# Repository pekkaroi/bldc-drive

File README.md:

# bldc-drive

This is a project developing a simple BLDC servo controller. It is based on an STM32F103 microcontroller.

Some parts, especially the PID control loop is based on development done by user mcm_xyz in cnczone.com forum. Thank you! Check the thread http://www.cnczone.com/forums/open-source-controller-boards/283428-cnc.html 

## Disclaimer
This software and hardware is provided "AS IS", WITHOUT ANY WARRANTY. The software is released under GPL v2. Authors accept no liability for any harm or loss resulting from use of this hardware or software.

## Authors & Contributors
* original Software by mcm_xyz from cnczone
* first Version of Hardware&Software in a Git-repo from pekkaroi via https://github.com/pekkaroi
* Schematic-additions and fork by Philipp Hörauf via https://github.com/Virtex7

## Firmware
Firmware is a work-in-progress (and will be for a while :), however following features are included:
* Trapezoidal BLDC commutation using either HALL sensors or quadrature encoder.
* Step+Dir input interface with PID position control loop.
* PWM+Dir input interface in velocity mode.
* USART communitacation for configuration. Configuration settings saved to flash memory.
* TODO: Motor Test Mode to simply activate a Motor with a fixed frequency, no encoder needed

### Update 1st May 2016
Some updates to the firmware. 
* ADC current limiting implemented. Appears to work OK
* I created a quick and ugly Python gui for tuning
* Updated the PID loop to have feedfoward coefficients FF1 and FF2 (like LinuxCNC). This means that the PID output can be adjusted by the requested speed and the requested acceleration. This made the PID tuning a lot easier for me at least, I'm able to get a motor to follow the requested position very well also during acceleration and during constant drive.

## Hardware:
First prototype hardware is built and it is working well. However, there are couple of known issues:
* 6n137 optocoupler is not officially supporting 3.3V supply voltage which is used in the board. In reality they seem to work, but the optocoupler should be changed or additional levelshifting circuitry added on next revision. Also, the optocoupler input circuit supports only push-pull-type encoder output. Many encoders seem to have open drain output. :(
* Few connectors in the layout missed solder stop openings. They were bit painfull to solder. :)
* The current amplifier INA27x connection is wrong. The IN+ and IN- should be swapped.

### STATUS QUO:

Second hardware revision with the above findings fixed is published. There are no known issues, two servo drives are succesfully driving my CNC router. Pics and videos to come..

### HARDWARE TODOs:

* verify all part-values into the schematic

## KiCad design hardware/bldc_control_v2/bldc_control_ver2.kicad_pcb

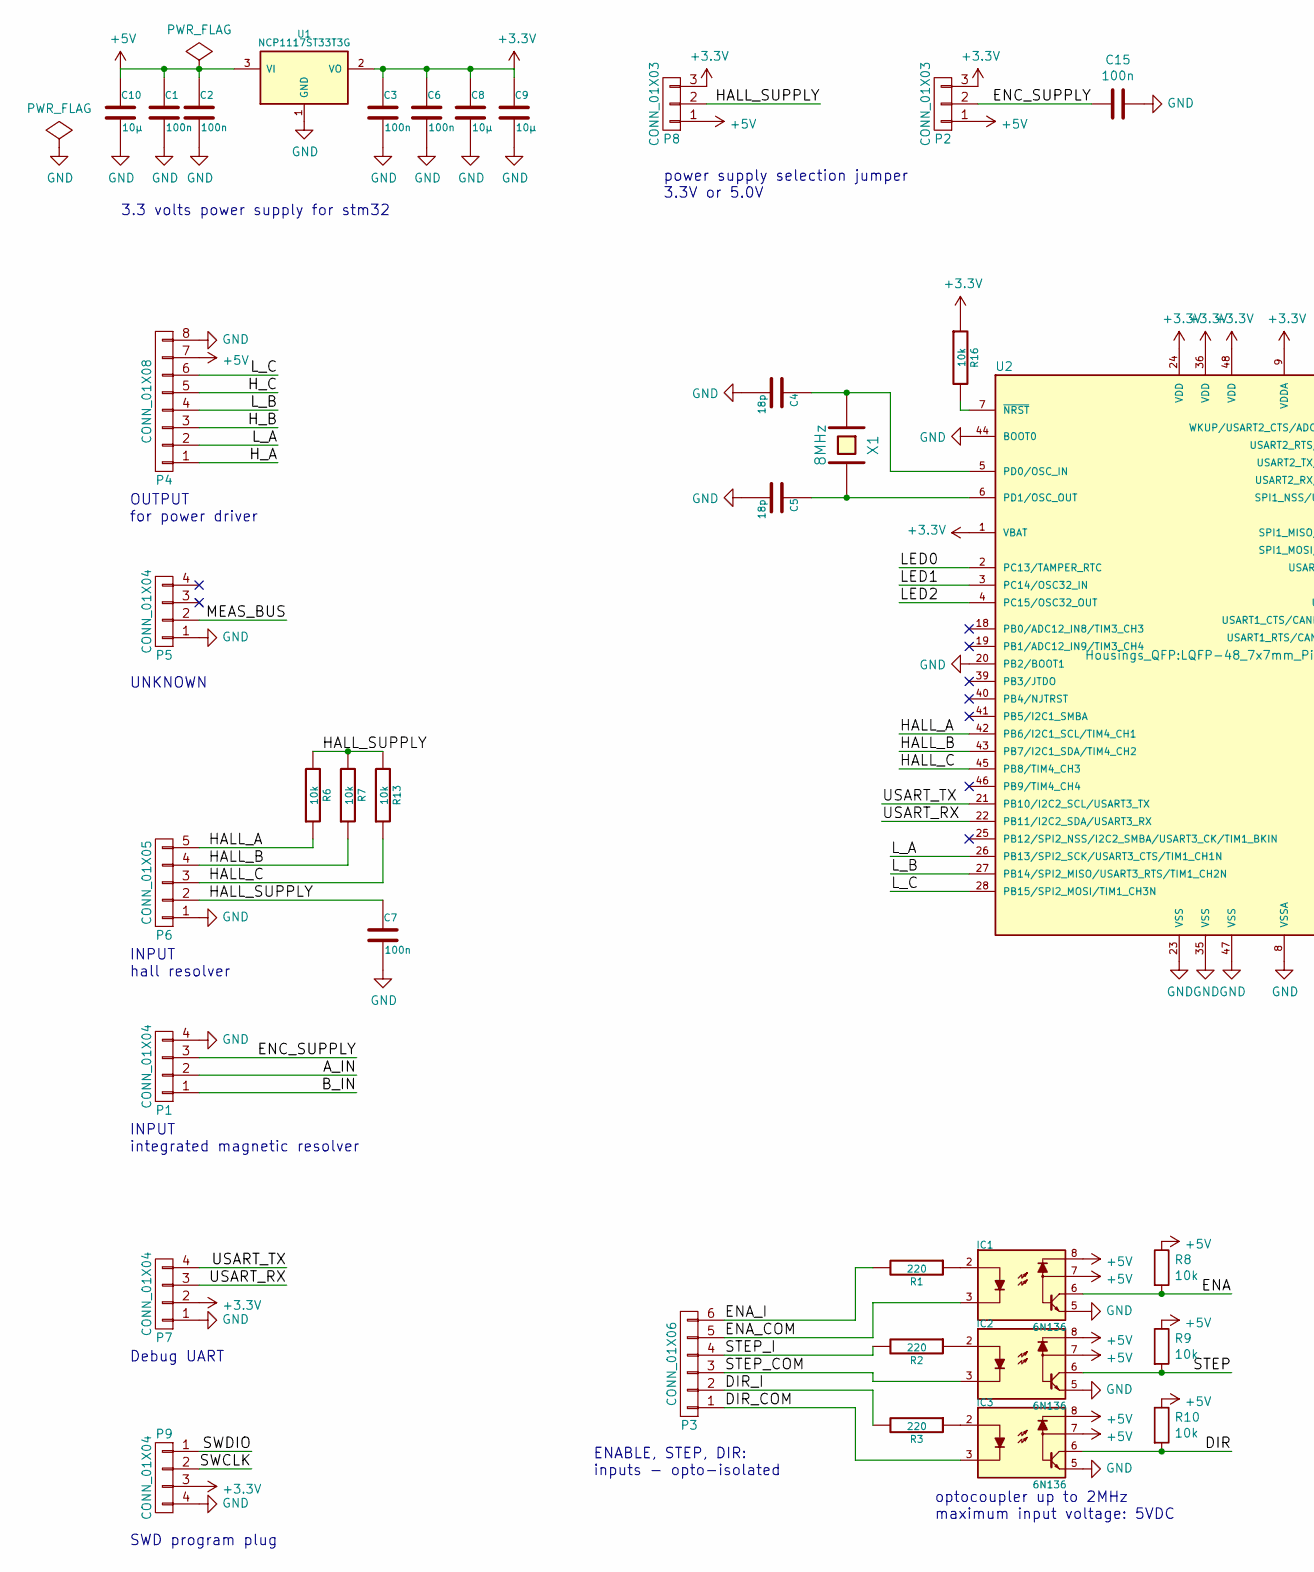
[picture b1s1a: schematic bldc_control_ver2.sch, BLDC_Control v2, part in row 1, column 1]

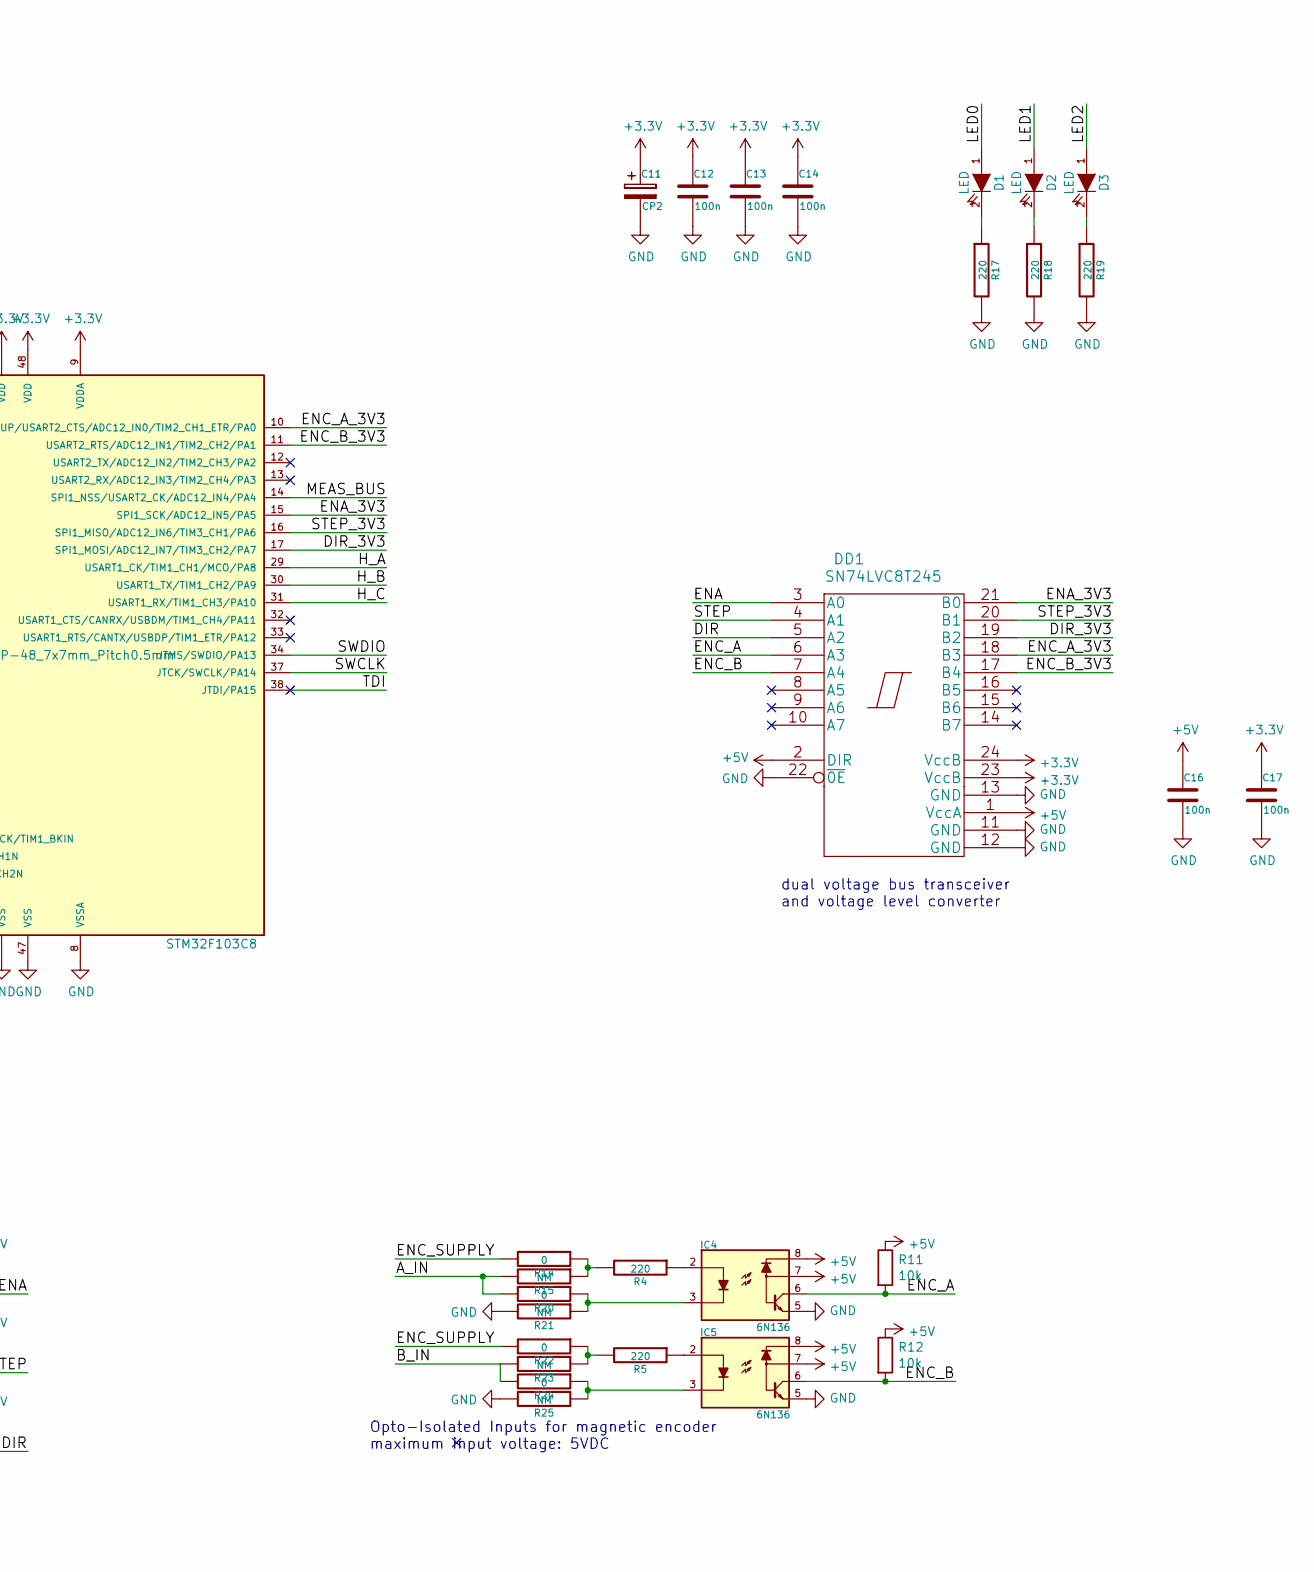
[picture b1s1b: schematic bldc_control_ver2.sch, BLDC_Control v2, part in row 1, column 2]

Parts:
C1, C2, C3, C6, C7, C12, C13, C14, C15, C17: 100n; C_0603
C4, C5: 18p; C_0603
C8, C9, C10: 10µ; C_0805
C11: CP2; TantalC_SizeC_EIA-6032_Reflow
C16: 100n; C_1206
D1, D2, D3: LED; LED_0603
DD1: SN74LVC8T245; SSOP-24_5.3x8.2mm_Pitch0.65mm
IC1, IC2, IC3, IC4, IC5: 6N136; SMD-8
P1: CONN_01X04; JST_PH_B4B-PH-K_04x2.00mm_Straight
P2, P8: CONN_01X03; Pin_Header_Straight_1x03
P3: CONN_01X06; Pin_Header_Straight_1x06
P4: CONN_01X08; JST_PH_B8B-PH-K_08x2.00mm_Straight
P5, P7: CONN_01X04; Pin_Header_Straight_1x04
P6: CONN_01X05; JST_XH_B05B-XH-A_05x2.50mm_Straight
P9: CONN_01X04; jst-ph-JST-PH4
R1, R2, R3, R4, R5, R17, R18, R19: 220; R_0603
R6, R7, R8, R9, R10, R11, R12, R13, R16: 10k; R_0603
R14, R20, R22, R24: 0; R_0603
R15, R21, R23, R25: NM; R_0603
U1: NCP1117ST33T3G; SOT-223-3Lead_TabPin2
U2: STM32F103C8; LQFP-48_7x7mm_Pitch0.5mm
X1: 8MHz; Crystal_HC49-SD_SMD

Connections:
+3V3: C3.1, C6.1, C8.1, C9.1, C11.1, C12.1, C13.1, C14.1, C17.1, DD1.23 (VccB), DD1.24 (VccB), P2.3, P7.2, P8.3, P9.3, R16.1, U1.2 (VO), U2.1 (VBAT), U2.9 (VDDA), U2.24 (VDD), U2.36 (VDD), U2.48 (VDD)
+5V: C1.1, C2.1, C10.1, C16.1, DD1.1 (VccA), DD1.2 (DIR), IC1.7, IC1.8, IC2.7, IC2.8, IC3.7, IC3.8, IC4.7, IC4.8, IC5.7, IC5.8, P2.1, P4.7, P8.1, R8.1, R9.1, R10.1, R11.1, R12.1, U1.3 (VI)
/A_IN: P1.2, R15.2, R20.2
/B_IN: P1.1, R23.2, R24.2
/DIR: DD1.5 (A2), IC3.6, R10.2
/DIR_3V3: DD1.19 (B2), U2.17 (SPI1_MOSI/ADC12_IN7/TIM3_CH2/PA7)
/DIR_COM: IC3.3, P3.1
/DIR_I: P3.2, R3.2
/ENA: DD1.3 (A0), IC1.6, R8.2
/ENA_3V3: DD1.21 (B0), U2.15 (SPI1_SCK/ADC12_IN5/PA5)
/ENA_COM: IC1.3, P3.5
/ENA_I: P3.6, R1.2
/ENC_A: DD1.6 (A3), IC4.6, R11.2
/ENC_A_3V3: DD1.18 (B3), U2.10 (WKUP/USART2_CTS/ADC12_IN0/TIM2_CH1_ETR/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)
/ENC_B: DD1.7 (A4), IC5.6, R12.2
/ENC_B_3V3: DD1.17 (B4), U2.11 (USART2_RTS/ADC12_IN1/TIM2_CH2/PA1)
/ENC_SUPPLY: C15.2, P1.3, P2.2, R14.2, R22.2
/HALL_A: P6.5, R6.1, U2.42 (PB6/I2C1_SCL/TIM4_CH1)
/HALL_B: P6.4, R7.1, U2.43 (PB7/I2C1_SDA/TIM4_CH2)
/HALL_C: P6.3, R13.1, U2.45 (PB8/TIM4_CH3)
/HALL_SUPPLY: C7.1, P6.2, P8.2, R6.2, R7.2, R13.2
/H_A: P4.1, U2.29 (USART1_CK/TIM1_CH1/MCO/PA8)
/H_B: P4.3, U2.30 (USART1_TX/TIM1_CH2/PA9)
/H_C: P4.5, U2.31 (USART1_RX/TIM1_CH3/PA10)
/LED0: D1.1 (A), U2.2 (PC13/TAMPER_RTC)
/LED1: D2.1 (A), U2.3 (PC14/OSC32_IN)
/LED2: D3.1 (A), U2.4 (PC15/OSC32_OUT)
/L_A: P4.2, U2.26 (PB13/SPI2_SCK/USART3_CTS/TIM1_CH1N)
/L_B: P4.4, U2.27 (PB14/SPI2_MISO/USART3_RTS/TIM1_CH2N)
/L_C: P4.6, U2.28 (PB15/SPI2_MOSI/TIM1_CH3N)
/MEAS_BUS: P5.2, U2.14 (SPI1_NSS/USART2_CK/ADC12_IN4/PA4)
/STEP: DD1.4 (A1), IC2.6, R9.2
/STEP_3V3: DD1.20 (B1), U2.16 (SPI1_MISO/ADC12_IN6/TIM3_CH1/PA6)
/STEP_COM: IC2.3, P3.3
/STEP_I: P3.4, R2.2
/SWCLK: P9.2, U2.37 (JTCK/SWCLK/PA14)
/SWDIO: P9.1, U2.34 (JTMS/SWDIO/PA13)
/TDI: U2.38 (JTDI/PA15)
/USART_RX: P7.3, U2.22 (PB11/I2C2_SDA/USART3_RX)
/USART_TX: P7.4, U2.21 (PB10/I2C2_SCL/USART3_TX)
GND: C1.2, C2.2, C3.2, C4.2, C5.2, C6.2, C7.2, C8.2, C9.2, C10.2, C11.2, C12.2, C13.2, C14.2, C15.1, C16.2, C17.2, DD1.11 (GND), DD1.12 (GND), DD1.13 (GND), DD1.22 (~0E), IC1.5, IC2.5, IC3.5, IC4.5, IC5.5, P1.4, P4.8, P5.1, P6.1, P7.1, P9.4, R17.2, R18.2, R19.2, R21.2, R25.2, U1.1 (GND), U2.8 (VSSA), U2.20 (PB2/BOOT1), U2.23 (VSS), U2.35 (VSS), U2.44 (BOOT0), U2.47 (VSS)
unnamed: C4.1, U2.5 (PD0/OSC_IN), X1.1
unnamed: C5.1, U2.6 (PD1/OSC_OUT), X1.2
unnamed: D1.2 (K), R17.1
unnamed: D2.2 (K), R18.1
unnamed: D3.2 (K), R19.1
unnamed: IC1.2, R1.1
unnamed: IC2.2, R2.1
unnamed: IC3.2, R3.1
unnamed: IC4.2, R4.1
unnamed: IC4.3, R20.1, R21.1
unnamed: IC5.2, R5.1
unnamed: IC5.3, R24.1, R25.1
unnamed: R4.2, R14.1, R15.1
unnamed: R16.2, U2.7 (~NRST)
unnamed: R5.2, R22.1, R23.1

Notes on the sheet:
3.3 volts power supply for stm32
SWD program plug
Debug UART
INPUT hall resolver
dual voltage bus transceiver and voltage level converter
power supply selection jumper 3.3V or 5.0V
ENABLE, STEP, DIR: inputs - opto-isolated
optocoupler up to 2MHz maximum input voltage: 5VDC
INPUT integrated magnetic resolver
Opto-Isolated Inputs for magnetic encoder maximum input voltage: 5VDC
OUTPUT for power driver
UNKNOWN

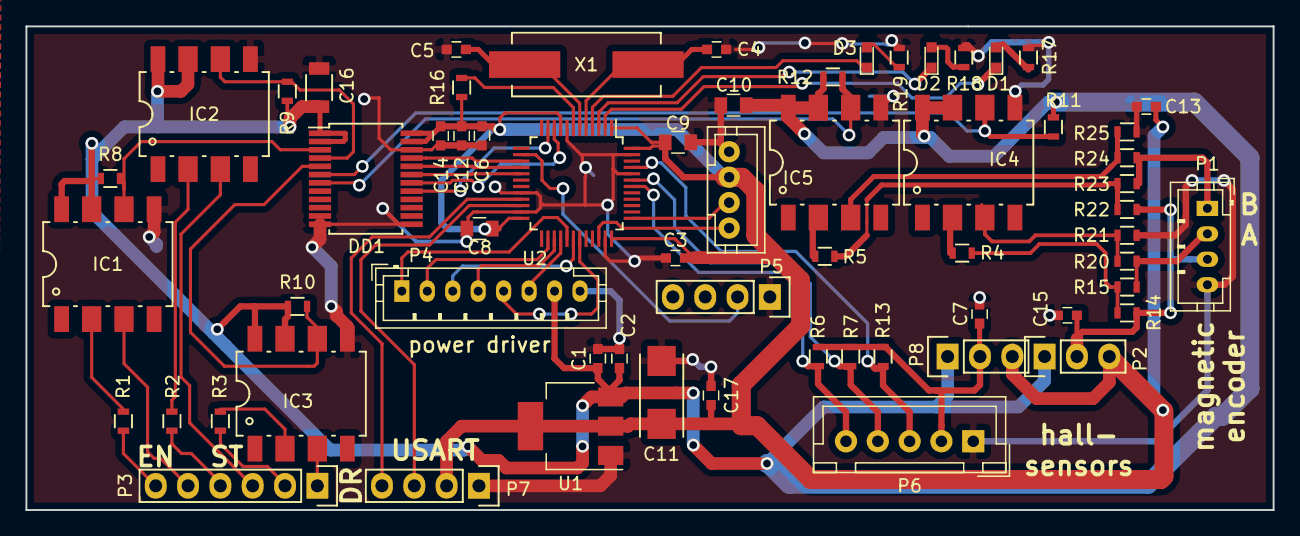
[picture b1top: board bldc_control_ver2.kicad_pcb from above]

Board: 2 copper layers, 98.0 x 38.0 mm, 63 parts (0 on the bottom side), 55 nets.

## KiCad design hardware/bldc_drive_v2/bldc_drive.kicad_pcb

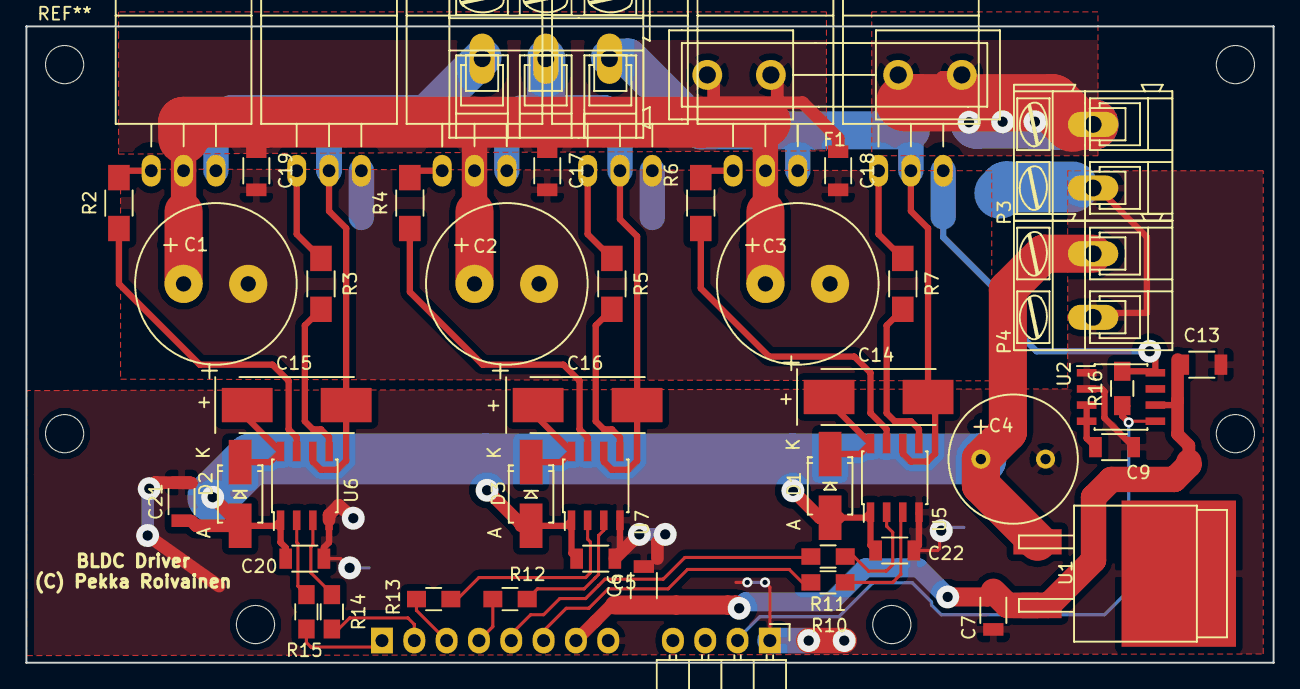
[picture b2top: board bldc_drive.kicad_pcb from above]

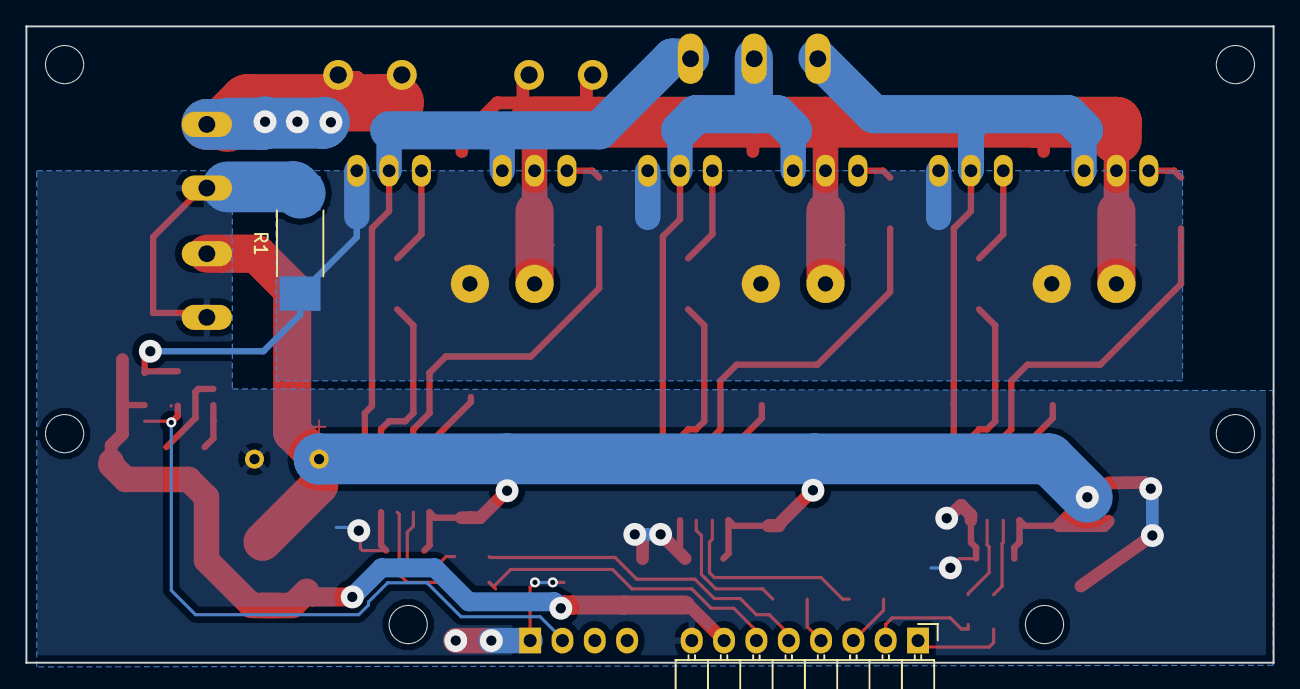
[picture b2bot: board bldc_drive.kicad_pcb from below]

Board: 2 copper layers, 98.0 x 50.0 mm, 52 parts (2 on the bottom side), 38 nets.

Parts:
C1, C2, C3: CP; Elko_vert_25x12.5mm_RM5
C4: CP; Elko_vert_20x10mm_RM5
C5, C6, C7, C9, C13, C17, C18, C19, C20, C21, C22: C; C_1206
C14, C15, C16: 22u; TantalC_SizeD_EIA-7343_HandSoldering
D1, D2, D3: UF4007; SMA_Handsoldering
F1: 10A?; Fuseholder5x20_horiz_open_inline_Type-I
P1: CONN_01X04; Pin_Header_Angled_1x04
P2: CONN_01X08; Pin_Header_Angled_1x08
P3, P4: CONN_01X02; AK300-2
P5: CONN_01X03; AK300-3
Q1, Q2, Q3, Q4, Q5, Q6: Q_NMOS_GDS; TO-220_Neutral123_Horizontal
R1: 10m; R_2512_HandSoldering
R2, R3, R4, R5, R6, R7: 10; R_1206_HandSoldering
R10, R11, R12, R13, R14, R15: 150; R_0805_HandSoldering
R16: NM; R_0805_HandSoldering
U1: 7805_NUMB; sot404
U2: INA27x; SOIC-8_3.9x4.9mm_Pitch1.27mm
U5, U6, U7: IR2101; SOIC-8_3.9x4.9mm_Pitch1.27mm

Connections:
+5V: C6.1, C7.1, C13.1, P2.7, U1.3, U2.6
+12V: C4.1, C5.1, C20.1, C21.1, C22.1, D1.2, D2.2, D3.2, P4.2, U1.1, U5.1, U6.1, U7.1
+48V: C1.1, C2.1, C3.1, C17.1, C18.1, C19.1, F1.2, Q1.2, Q3.2, Q5.2
/H_A: R15.1, U6.2
/H_B: R13.1, U7.2
/H_C: R11.1, U5.2
/L_A: R14.1, U6.3
/L_B: R12.1, U7.3
/L_C: R10.1, U5.3
/MEAS_BUS: P1.2, R16.1, U2.5
/MOTOR_A: C15.2, P5.1, Q1.3, Q2.2, U6.6
/MOTOR_B: C16.2, P5.2, Q3.3, Q4.2, U7.6
/MOTOR_C: C14.2, P5.3, Q5.3, Q6.2, U5.6
GND: C4.2, C5.2, C6.2, C7.2, C9.2, C13.2, C20.2, C21.2, C22.2, P1.1, P2.8, P3.1, P4.1, R1.2, U1.2, U2.1, U2.2, U5.4, U6.4, U7.4
GNDPWR: C1.2, C2.2, C3.2, C17.2, C18.2, C19.2, Q2.3, Q4.3, Q6.3, R1.1, R16.2, U2.8
unnamed: C9.1, U2.3, U2.4
unnamed: C14.1, D1.1, U5.8
unnamed: C15.1, D2.1, U6.8
unnamed: C16.1, D3.1, U7.8
unnamed: F1.1, P3.2
unnamed: P2.1, R15.2
unnamed: P2.2, R14.2
unnamed: P2.3, R13.2
unnamed: P2.4, R12.2
unnamed: P2.5, R11.2
unnamed: P2.6, R10.2
unnamed: Q1.1, R2.2
unnamed: Q2.1, R3.1
unnamed: Q3.1, R4.2
unnamed: Q4.1, R5.1
unnamed: Q5.1, R6.2
unnamed: Q6.1, R7.1
unnamed: R2.1, U6.7
unnamed: R3.2, U6.5
unnamed: R4.1, U7.7
unnamed: R5.2, U7.5
unnamed: R6.1, U5.7
unnamed: R7.2, U5.5

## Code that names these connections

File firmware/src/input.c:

/*
 	bldc-drive Cheap and simple brushless DC motor driver designed for CNC applications using STM32 microcontroller.
	Copyright (C) 2015 Pekka Roivainen

	This program is free software; you can redistribute it and/or
	modify it under the terms of the GNU General Public License
	as published by the Free Software Foundation; either version 2
	of the License, or (at your option) any later version.

	This program is distributed in the hope that it will be useful,
	but WITHOUT ANY WARRANTY; without even the implied warranty of
	MERCHANTABILITY or FITNESS FOR A PARTICULAR PURPOSE.  See the
	GNU General Public License for more details.

	You should have received a copy of the GNU General Public License
	along with this program; if not, write to the Free Software
	Foundation, Inc., 51 Franklin Street, Fifth Floor, Boston, MA  02110-1301, USA.
*/


#include <stm32f10x_gpio.h>
#include <stm32f10x_tim.h>
#include <stm32f10x_rcc.h>
#include <stm32f10x_exti.h>

#include "pwm.h"
#include "encoder.h"
#include "pid.h"
#include "input.h"
#include "configuration.h"

volatile uint16_t updateCtr;

volatile uint16_t motor_running;

void initLeds()
{
	RCC_APB2PeriphClockCmd(RCC_APB2Periph_GPIOC,ENABLE);
	GPIO_InitTypeDef GPIO_InitStructure;
	//LED0 == ENABLE Led
	GPIO_StructInit(&GPIO_InitStructure);
	GPIO_InitStructure.GPIO_Pin = GPIO_Pin_13;
	GPIO_InitStructure.GPIO_Mode = GPIO_Mode_Out_PP;
	GPIO_Init(GPIOC, &GPIO_InitStructure);
	//LED1 == ERROR Led
	GPIO_StructInit(&GPIO_InitStructure);
	GPIO_InitStructure.GPIO_Pin = GPIO_Pin_14;
	GPIO_InitStructure.GPIO_Mode = GPIO_Mode_Out_PP;
	GPIO_Init(GPIOC, &GPIO_InitStructure);
	//LED2 == POWER Led
	GPIO_StructInit(&GPIO_InitStructure);
	GPIO_InitStructure.GPIO_Pin = GPIO_Pin_15;
	GPIO_InitStructure.GPIO_Mode = GPIO_Mode_Out_PP;
	GPIO_Init(GPIOC, &GPIO_InitStructure);

}
void initStepDirInput()
{
	GPIO_InitTypeDef GPIO_InitStructure;

	//PA6 as STEP input
	GPIO_StructInit(&GPIO_InitStructure);
	GPIO_InitStructure.GPIO_Pin = GPIO_Pin_6;
	GPIO_InitStructure.GPIO_Mode = GPIO_Mode_IPD;
	GPIO_Init(GPIOA, &GPIO_InitStructure);

	//PA7 as DIR pin
	GPIO_StructInit(&GPIO_InitStructure);
	GPIO_InitStructure.GPIO_Pin = GPIO_Pin_7;
	GPIO_InitStructure.GPIO_Mode = GPIO_Mode_IPD;
	GPIO_Init(GPIOA, &GPIO_InitStructure);

	//PA5 as ENA pin
	GPIO_StructInit(&GPIO_InitStructure);
	GPIO_InitStructure.GPIO_Pin = GPIO_Pin_5;
	GPIO_InitStructure.GPIO_Mode = GPIO_Mode_IPD;
	GPIO_Init(GPIOA, &GPIO_InitStructure);

	GPIO_EXTILineConfig(GPIO_PortSourceGPIOA, GPIO_PinSource6); //STEP pin
	GPIO_EXTILineConfig(GPIO_PortSourceGPIOA, GPIO_PinSource5); //ENA pin

	EXTI_InitTypeDef EXTI_initStructure;
	EXTI_initStructure.EXTI_Line = EXTI_Line6;
	EXTI_initStructure.EXTI_Mode = EXTI_Mode_Interrupt;

if(!is_step_inverted)
	EXTI_initStructure.EXTI_Trigger = EXTI_Trigger_Rising;
else
	EXTI_initStructure.EXTI_Trigger = EXTI_Trigger_Falling;


	EXTI_initStructure.EXTI_LineCmd = ENABLE;
	EXTI_Init(&EXTI_initStructure);

	EXTI_initStructure.EXTI_Line = EXTI_Line5;
	EXTI_initStructure.EXTI_Mode = EXTI_Mode_Interrupt;
	EXTI_initStructure.EXTI_Trigger = EXTI_Trigger_Rising_Falling;
	EXTI_initStructure.EXTI_LineCmd = ENABLE;
	EXTI_Init(&EXTI_initStructure);

	NVIC_InitTypeDef nvicStructure;
	nvicStructure.NVIC_IRQChannel = EXTI9_5_IRQn;
	nvicStructure.NVIC_IRQChannelPreemptionPriority = 0;
	nvicStructure.NVIC_IRQChannelSubPriority = 2;
	nvicStructure.NVIC_IRQChannelCmd = ENABLE;
	NVIC_Init(&nvicStructure);
}

void EXTI9_5_IRQHandler()
{
	uint8_t ena,idir;

	if(EXTI_GetITStatus(EXTI_Line5)!= RESET)
	{
		//ENA PIN INTERRUPT
if(!is_ena_inverted)
		ena = GPIO_ReadInputDataBit(GPIOA, GPIO_Pin_5);
else
		ena = (~(GPIO_ReadInputDataBit(GPIOA, GPIO_Pin_5)))&1;

		if(ena && !motor_running)
		{

			//enable rose. Start
			pid_requested_position = encoder_count; //reset the desired position to current.
			pwm_motorStart();

			ENABLE_LED_ON;
			ERROR_LED_OFF;
		}
		else if(!ena && motor_running)
		{
			//enable fell. Stop.
			pwm_motorStop();
			ENABLE_LED_OFF;
		}
		else if(!ena)
		{
			ENABLE_LED_OFF;
		}
		EXTI_ClearITPendingBit(EXTI_Line5);
	}

	if(EXTI_GetITStatus(EXTI_Line6)!= RESET)
	{
		//STEP PIN INTERRUPT

if(!is_dir_inverted)
		idir = GPIO_ReadInputDataBit(GPIOA, GPIO_Pin_7);
else
		idir = (~(GPIO_ReadInputDataBit(GPIOA, GPIO_Pin_7)))&1;

		if(idir)
		{
			pid_requested_position+=s.encoder_counts_per_step;
		}
		else
			pid_requested_position-=s.encoder_counts_per_step;
		EXTI_ClearITPendingBit(EXTI_Line6);
	}

}

void initPWMInput()
{

	GPIO_InitTypeDef GPIO_InitStructure;

	//TIM3 as PWM input
	GPIO_StructInit(&GPIO_InitStructure);
	GPIO_InitStructure.GPIO_Pin = GPIO_Pin_6;
	GPIO_InitStructure.GPIO_Mode = GPIO_Mode_IPD;
	GPIO_Init(GPIOA, &GPIO_InitStructure);

	//PA7 as DIR pin
	GPIO_StructInit(&GPIO_InitStructure);
	GPIO_InitStructure.GPIO_Pin = GPIO_Pin_7;
	GPIO_InitStructure.GPIO_Mode = GPIO_Mode_IPD;
	GPIO_Init(GPIOA, &GPIO_InitStructure);

	//PA5 as ENA pin
	GPIO_StructInit(&GPIO_InitStructure);
	GPIO_InitStructure.GPIO_Pin = GPIO_Pin_5;
	GPIO_InitStructure.GPIO_Mode = GPIO_Mode_IPD;
	GPIO_Init(GPIOA, &GPIO_InitStructure);

	EXTI_InitTypeDef EXTI_initStructure;
	EXTI_initStructure.EXTI_Line = EXTI_Line5;
	EXTI_initStructure.EXTI_Mode = EXTI_Mode_Interrupt;
	EXTI_initStructure.EXTI_Trigger = EXTI_Trigger_Rising_Falling;
	EXTI_initStructure.EXTI_LineCmd = ENABLE;
	EXTI_Init(&EXTI_initStructure);

	NVIC_InitTypeDef nvicStructure;
	nvicStructure.NVIC_IRQChannel = EXTI9_5_IRQn;
	nvicStructure.NVIC_IRQChannelPreemptionPriority = 0;
	nvicStructure.NVIC_IRQChannelSubPriority = 2;
	nvicStructure.NVIC_IRQChannelCmd = ENABLE;
	NVIC_Init(&nvicStructure);


	RCC_APB1PeriphClockCmd(RCC_APB1Periph_TIM3, ENABLE);
	TIM_TimeBaseInitTypeDef TIM_TimeBaseStructure;
	TIM_TimeBaseStructInit(&TIM_TimeBaseStructure);
	TIM_TimeBaseStructure.TIM_Prescaler = 1;
	TIM_TimeBaseStructure.TIM_CounterMode = TIM_CounterMode_Up;
	TIM_TimeBaseStructure.TIM_Period = 65535;
	TIM_TimeBaseStructure.TIM_ClockDivision = 0;
	TIM_TimeBaseStructure.TIM_RepetitionCounter = 0;
	TIM_TimeBaseInit(TIM3, &TIM_TimeBaseStructure);



	TIM_ICInitTypeDef TIM_ICInit;
if(!is_step_inverted)
	TIM_ICInit.TIM_ICPolarity = TIM_ICPolarity_Rising;
else
	TIM_ICInit.TIM_ICPolarity = TIM_ICPolarity_Falling;

	TIM_ICInit.TIM_ICFilter = 5;
	TIM_ICInit.TIM_Channel = TIM_Channel_1;
	TIM_ICInit.TIM_ICPrescaler = TIM_ICPSC_DIV1;
	TIM_ICInit.TIM_ICSelection = TIM_ICSelection_DirectTI;

	TIM_PWMIConfig(TIM3, &TIM_ICInit);
	TIM_CCxCmd(TIM3, TIM_Channel_1, ENABLE);
	TIM_CCxCmd(TIM3, TIM_Channel_2, ENABLE);

	TIM_SelectInputTrigger(TIM3,TIM_TS_TI1FP1);
	TIM_SelectSlaveMode(TIM3, TIM_SlaveMode_Reset);
	TIM_ITConfig(TIM3, TIM_IT_CC1 | TIM_IT_Update, ENABLE);
	TIM_Cmd(TIM3,ENABLE);
	NVIC_InitTypeDef NVIC_InitStructure;
	NVIC_InitStructure.NVIC_IRQChannel = TIM3_IRQn;
	NVIC_InitStructure.NVIC_IRQChannelPreemptionPriority = 0x01;
	NVIC_InitStructure.NVIC_IRQChannelSubPriority = 3;
	NVIC_InitStructure.NVIC_IRQChannelCmd = ENABLE;
	NVIC_Init(&NVIC_InitStructure);
}


void TIM3_IRQHandler(void) {
  if (TIM_GetITStatus(TIM3, TIM_IT_Update) != RESET)
  {
	if(s.inputMethod==inputMethod_stepDir)
	{
	  updatePid();
	  TIM_ClearITPendingBit(TIM3, TIM_IT_Update);
	}
	else
	{
		TIM_ClearITPendingBit(TIM3, TIM_IT_Update);
		updateCtr++;
		if(updateCtr>50)
		{
			 //pwm_motorStop();
			 //ERROR_LED_ON;

		}

	}

  }
  if (TIM_GetITStatus(TIM3, TIM_IT_CC1) != RESET)
  {

	uint16_t tim3_dc = TIM3->CCR2;
	uint16_t tim3_per = TIM3->CCR1;

	uint16_t DC;
	if(!is_dir_inverted)
		dir = GPIO_ReadInputDataBit(GPIOA, GPIO_Pin_7);
	else
		dir = (~(GPIO_ReadInputDataBit(GPIOA, GPIO_Pin_7)))&1;


	if(tim3_per>0 && tim3_per>tim3_dc)
	{
	  DC = ((uint32_t)(BLDC_CHOPPER_PERIOD*tim3_dc)/(uint32_t)tim3_per);
	}
	else
	  DC=0;

	//if(DC<BLDC_NOL*3) DC=BLDC_NOL*3;

	duty = DC;
	updateCtr=0;
#ifndef SINUSOID_DRIVE
	pwm_setDutyCycle();
#endif
	TIM_ClearITPendingBit(TIM3, TIM_IT_CC1);

  }
}

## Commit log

2015-11-14 GPLv2 license information added
2015-11-14 added hardware
2015-11-15 added pdfs of schematics
2015-11-15 Cleanup + bug fixes in PWM input mode
2016-05-01 Major firmware update
2016-05-26 PCB ver2. Added Gui
2016-08-01 Implemented delay_ms using SysTick
2016-08-03 removed stupid variable declarations from headers
2016-08-03 few more changes to make this compile with IAR
2016-08-29 Serial streaming added for encoder commutation mode
2016-09-08 Initial release of sinusoid drive
2016-09-08 Deleted hall.h, not needed in sinusoid
2016-09-08 WTF, I suck in git
2016-09-08 adding hall.h
2016-09-08 deleted hall.h from sinudoid drive
2016-09-08 bugfix: s.max_error did not have any effect
2016-09-11 cleanup
2016-10-02 Bug fixed in forceInitialization
2017-02-20 first: remove old versions of the hardware - git history rulez. second: made schematic a bit more readable... third: migrated schematic to KiCAD 4
2017-02-20 added TODOs to the readme.md
2017-02-20 tempfiles vom KiCAD entfernt und Bauteilwerte ausgedacht...
2017-02-20 added authors section to README
2017-02-20 schaltplan und layout angepasst
2017-02-21 hardware: bldc_control_v3 release. firmware: combined the sinusoid_drive branch to master. select between trapezoidal commutation and sinusoid drive in configuration.h
2017-12-08 adding precompiled binaries
2017-12-08 oops, add correct binary
2018-01-18 Misc. refactoring and improvements. Added pid_deadband parameter.
